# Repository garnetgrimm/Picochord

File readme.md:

# Picochord
An open source digital Omnichord clone based on the Raspberry Pi Pico. The firmware is currently configured to only generate audio from the input signals, but usb/analog midi support is in the works for the near future.

## Building the Firmware
The getting started guide has detailed instructions for building on each OS. https://datasheets.raspberrypi.com/pico/getting-started-with-pico.pdf

You will likely have to cd into the build directory to configure cmake and build.

## Circuits
The entire Picochord is comprised of three main subcircuits, all driven by the pico. 

* Keypad
* Strumpad
* Speaker amplifier

The PCB directory contains simulations, schematics, PCB's and screenshots for each of the circuits. The schematics/PCBs can be viewed with KiCad 6.0

## Chassis
The PCB's were screwed directly into a acrylic board. The only other required pieces were a battery holder and speaker holder which I have included STL's and FreeCad files for.

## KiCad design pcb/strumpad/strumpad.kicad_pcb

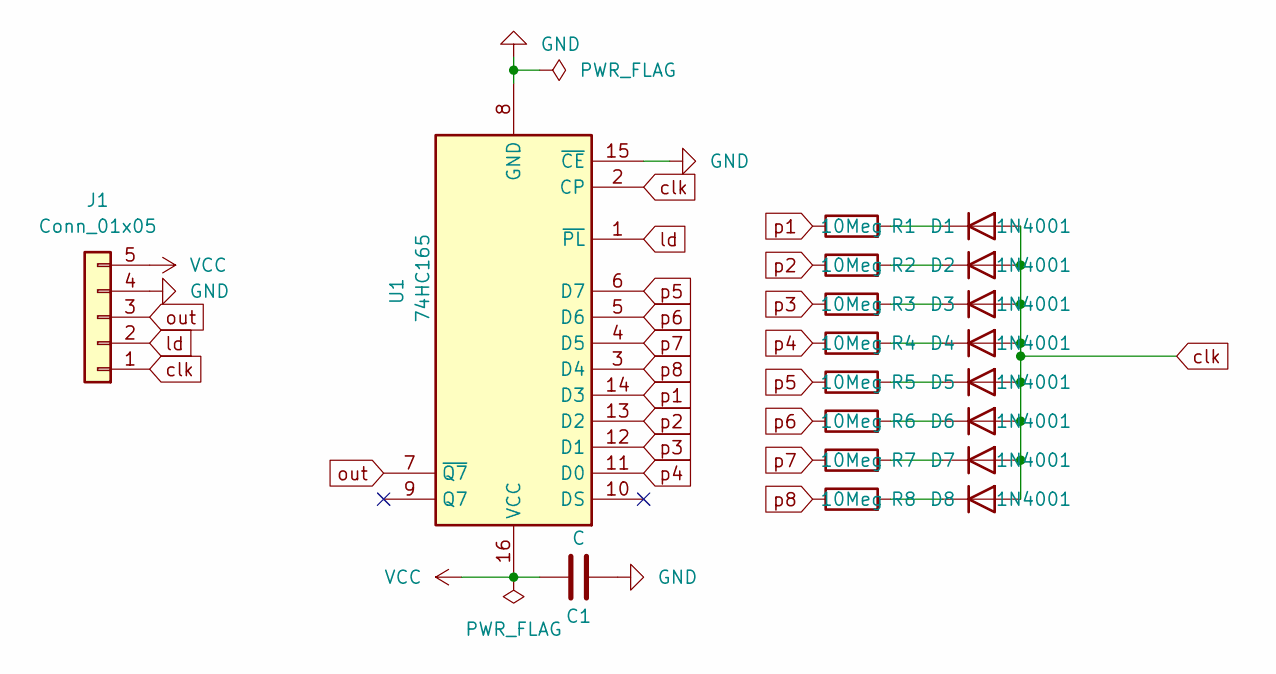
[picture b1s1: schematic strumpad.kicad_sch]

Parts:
C1: C; CP_Radial_D5.0mm_P2.50mm
D1, D2, D3, D4, D5, D6, D7, D8: 1N4001; D_DO-41_SOD81_P10.16mm_Horizontal
J1: Conn_01x05; PinSocket_1x05_P2.54mm_Vertical
R1, R2, R3, R4, R5, R6, R7, R8: 10Meg; R_Axial_DIN0204_L3.6mm_D1.6mm_P5.08mm_Horizontal
U1: 74HC165; DIP-16_W7.62mm_Socket

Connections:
GND: C1.2, J1.4, U1.8 (GND), U1.15 (~CE)
unnamed: D1.1 (K), R1.2
unnamed: D2.1 (K), R2.2
unnamed: D3.1 (K), R3.2
unnamed: D4.1 (K), R4.2
unnamed: D5.1 (K), R5.2
unnamed: D6.1 (K), R6.2
unnamed: D7.1 (K), R7.2
unnamed: D8.1 (K), R8.2
VCC: C1.1, J1.5, U1.16 (VCC)
clk: D1.2 (A), D2.2 (A), D3.2 (A), D4.2 (A), D5.2 (A), D6.2 (A), D7.2 (A), D8.2 (A), J1.1, U1.2 (CP)
ld: J1.2, U1.1 (~PL)
out: J1.3, U1.7 (~Q7)
p1: R1.1, U1.14 (D3)
p2: R2.1, U1.13 (D2)
p3: R3.1, U1.12 (D1)
p4: R4.1, U1.11 (D0)
p5: R5.1, U1.6 (D7)
p6: R6.1, U1.5 (D6)
p7: R7.1, U1.4 (D5)
p8: R8.1, U1.3 (D4)

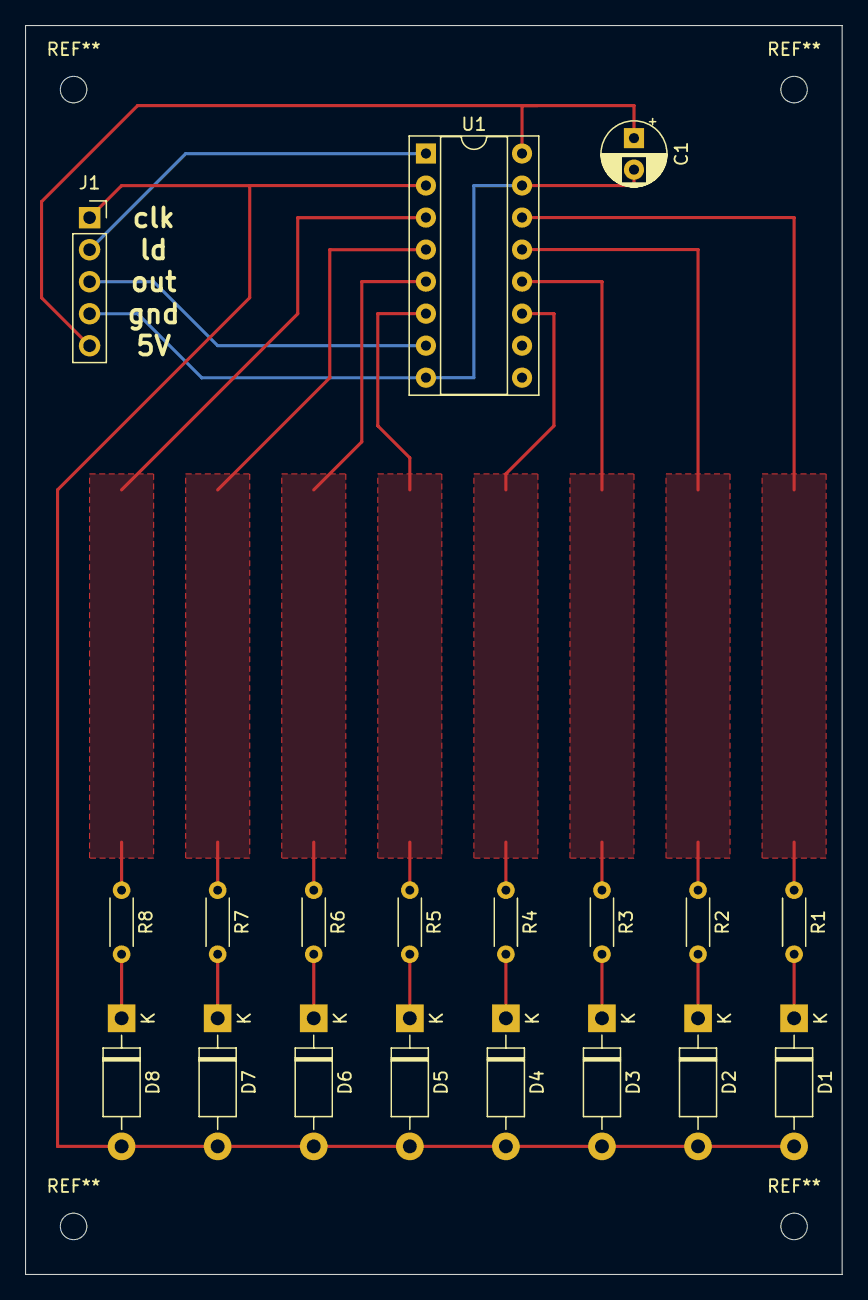
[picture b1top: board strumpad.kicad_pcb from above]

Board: 2 copper layers, 64.8 x 99.1 mm, 19 parts (0 on the bottom side), 21 nets.

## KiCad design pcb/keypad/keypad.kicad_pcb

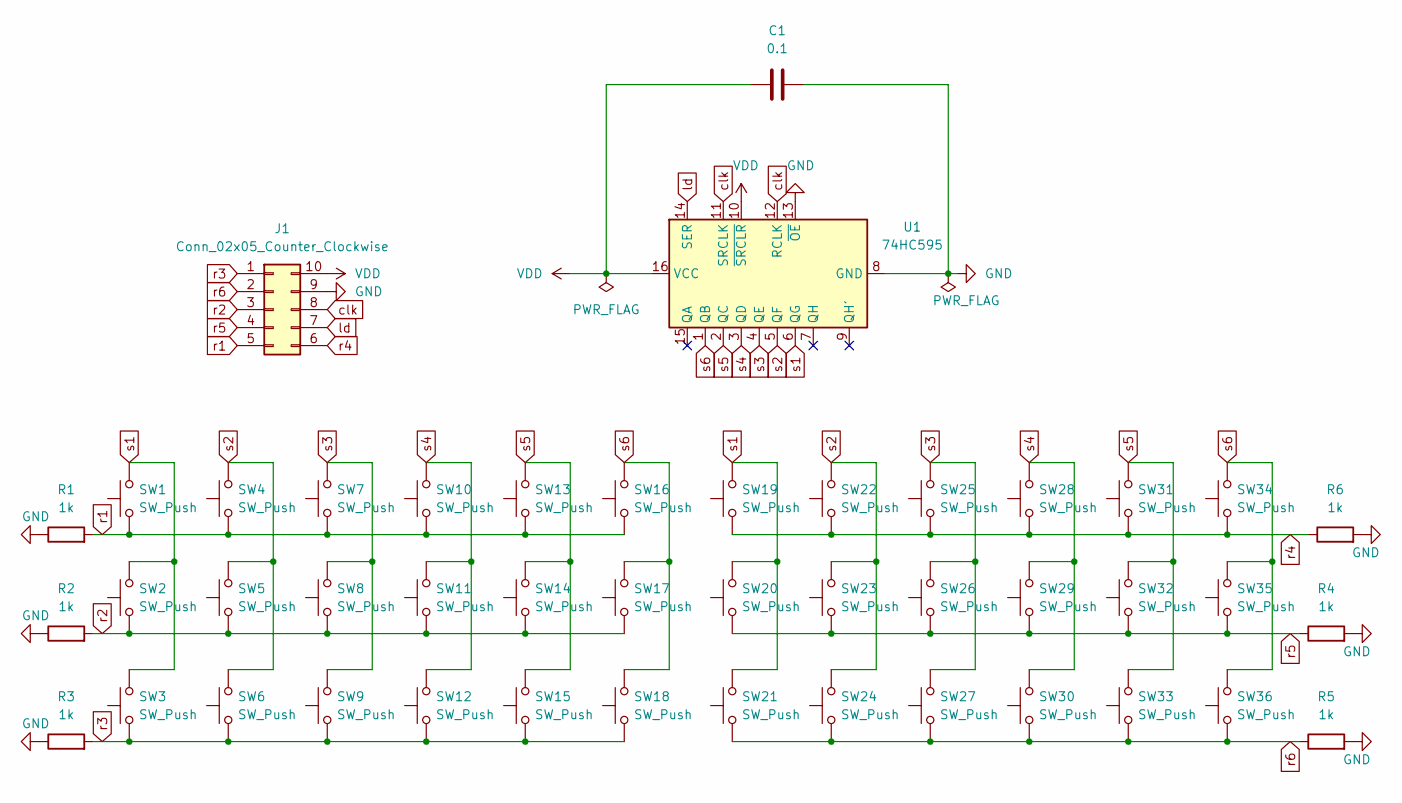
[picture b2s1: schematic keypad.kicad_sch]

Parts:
C1: 0.1; CP_Radial_D5.0mm_P2.50mm
J1: Conn_02x05_Counter_Clockwise; PinSocket_2x05_P2.54mm_Vertical
R1, R2, R3, R4, R5, R6: 1k; R_Axial_DIN0207_L6.3mm_D2.5mm_P2.54mm_Vertical
SW1, SW2, SW3, SW4, SW5, SW6, SW7, SW8, SW9, SW10, SW11, SW12, SW13, SW14, SW15, SW16, SW17, SW18, SW19, SW20, SW21, SW22, SW23, SW24, SW25, SW26, SW27, SW28, SW29, SW30, SW31, SW32, SW33, SW34, SW35, SW36: SW_Push; SW_PUSH_6mm
U1: 74HC595; DIP-16_W7.62mm_Socket

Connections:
GND: C1.2, J1.9, R1.1, R2.1, R3.1, R4.2, R5.2, R6.2, U1.8 (GND), U1.13 (~OE)
VDD: C1.1, J1.10, U1.10 (~SRCLR), U1.16 (VCC)
clk: J1.8, U1.11 (SRCLK), U1.12 (RCLK)
ld: J1.7, U1.14 (SER)
r1: J1.5, R1.2, SW1.1, SW4.1, SW7.1, SW10.1, SW13.1, SW16.1
r2: J1.3, R2.2, SW2.1, SW5.1, SW8.1, SW11.1, SW14.1, SW17.1
r3: J1.1, R3.2, SW3.1, SW6.1, SW9.1, SW12.1, SW15.1, SW18.1
r4: J1.6, R6.1, SW19.1, SW22.1, SW25.1, SW28.1, SW31.1, SW34.1
r5: J1.4, R4.1, SW20.1, SW23.1, SW26.1, SW29.1, SW32.1, SW35.1
r6: J1.2, R5.1, SW21.1, SW24.1, SW27.1, SW30.1, SW33.1, SW36.1
s1: SW1.2, SW2.2, SW3.2, SW19.2, SW20.2, SW21.2, U1.6 (QG)
s2: SW4.2, SW5.2, SW6.2, SW22.2, SW23.2, SW24.2, U1.5 (QF)
s3: SW7.2, SW8.2, SW9.2, SW25.2, SW26.2, SW27.2, U1.4 (QE)
s4: SW10.2, SW11.2, SW12.2, SW28.2, SW29.2, SW30.2, U1.3 (QD)
s5: SW13.2, SW14.2, SW15.2, SW31.2, SW32.2, SW33.2, U1.2 (QC)
s6: SW16.2, SW17.2, SW18.2, SW34.2, SW35.2, SW36.2, U1.1 (QB)

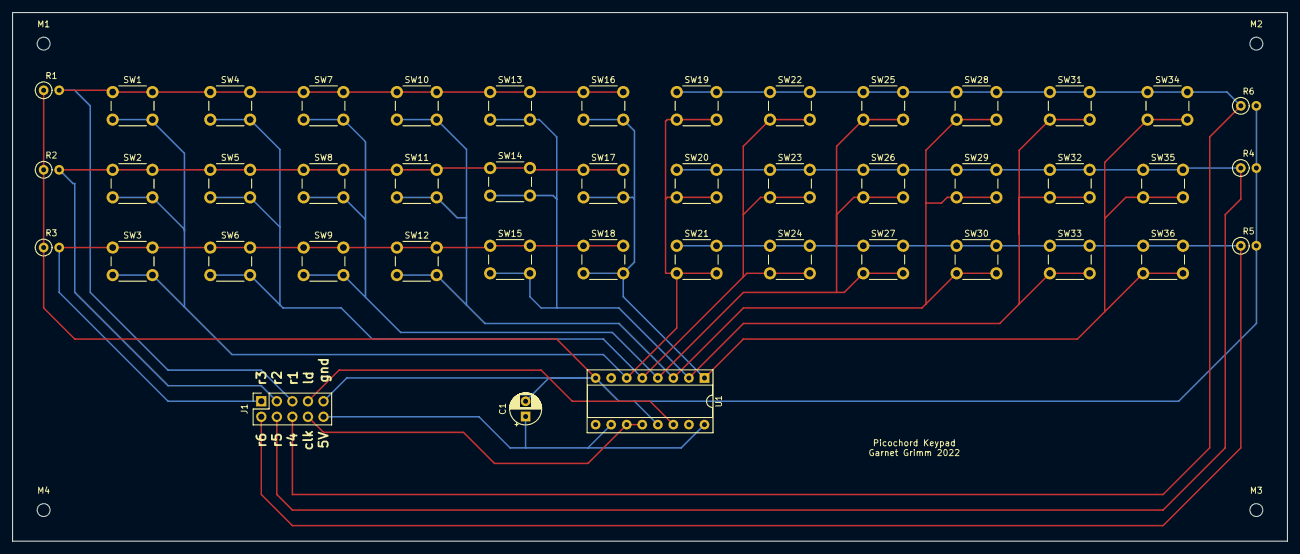
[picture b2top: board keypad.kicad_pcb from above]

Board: 2 copper layers, 208.3 x 86.4 mm, 49 parts (0 on the bottom side), 16 nets.

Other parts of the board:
M1, M2, M3, M4: MountingHole_2.1mm

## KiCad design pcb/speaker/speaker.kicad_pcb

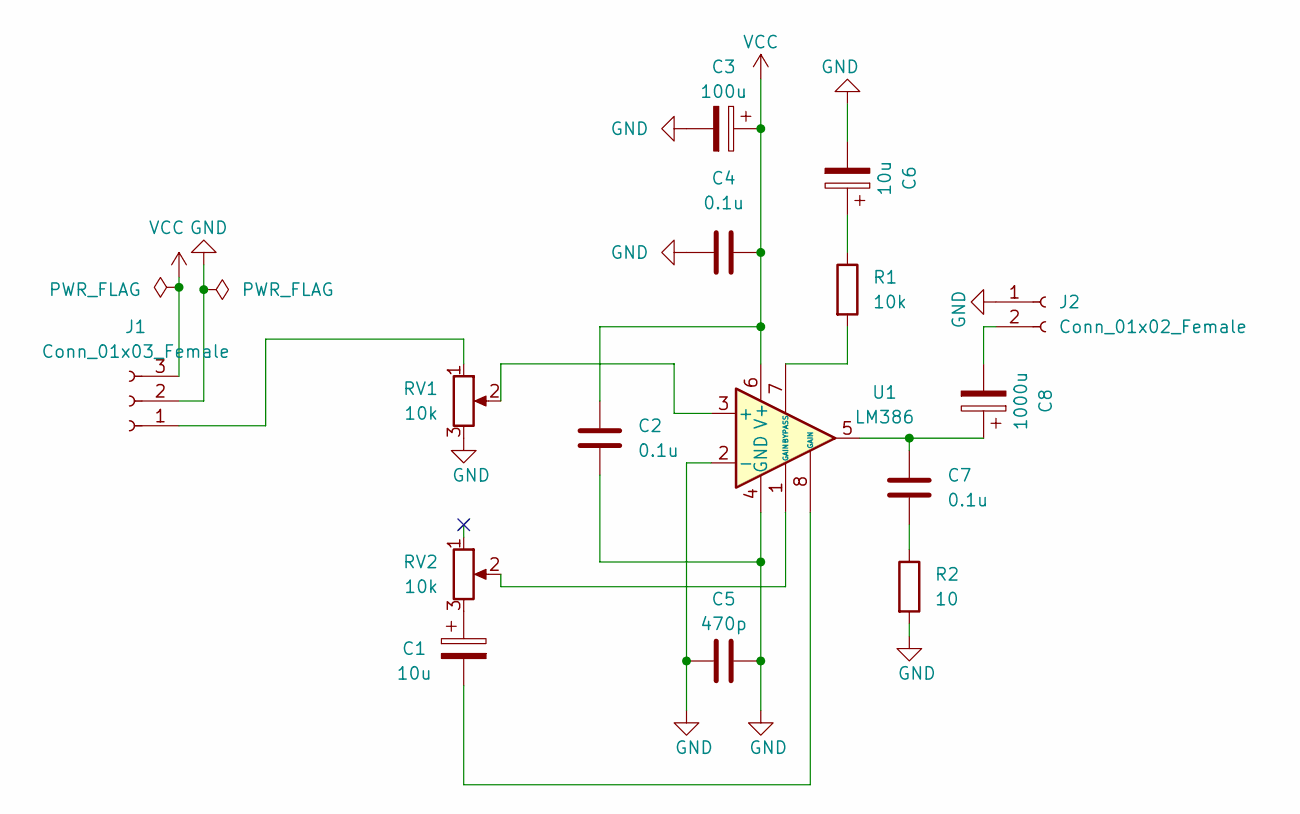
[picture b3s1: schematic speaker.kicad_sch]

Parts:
C1, C6: 10u; CP_Radial_D6.3mm_P2.50mm
C2, C4, C7: 0.1u; CP_Radial_D6.3mm_P2.50mm
C3: 100u; CP_Radial_D6.3mm_P2.50mm
C5: 470p; CP_Radial_D6.3mm_P2.50mm
C8: 1000u; CP_Radial_D6.3mm_P2.50mm
J1: Conn_01x03_Female; PinSocket_1x03_P2.54mm_Vertical
J2: Conn_01x02_Female; PinSocket_1x02_P2.54mm_Vertical
R1: 10k; R_Axial_DIN0207_L6.3mm_D2.5mm_P7.62mm_Horizontal
R2: 10; R_Axial_DIN0207_L6.3mm_D2.5mm_P7.62mm_Horizontal
RV1, RV2: 10k; Potentiometer_Alps_RK09Y11_Single_Horizontal
U1: LM386; DIP-8_W7.62mm_Socket

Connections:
GND: C2.1, C3.2, C4.1, C5.1, C5.2, C6.2, J1.2, J2.1, R2.2, RV1.3, U1.2 (-), U1.4 (GND)
unnamed: C1.1, RV2.3
unnamed: C1.2, U1.8 (GAIN)
unnamed: C6.1, R1.1
unnamed: C7.1, R2.1
unnamed: C7.2, C8.1, U1.5
unnamed: C8.2, J2.2
unnamed: R1.2, U1.7 (BYPASS)
unnamed: J1.1, RV1.1
unnamed: RV1.2, U1.3 (+)
unnamed: RV2.2, U1.1 (GAIN)
VCC: C2.2, C3.1, C4.2, J1.3, U1.6 (V+)

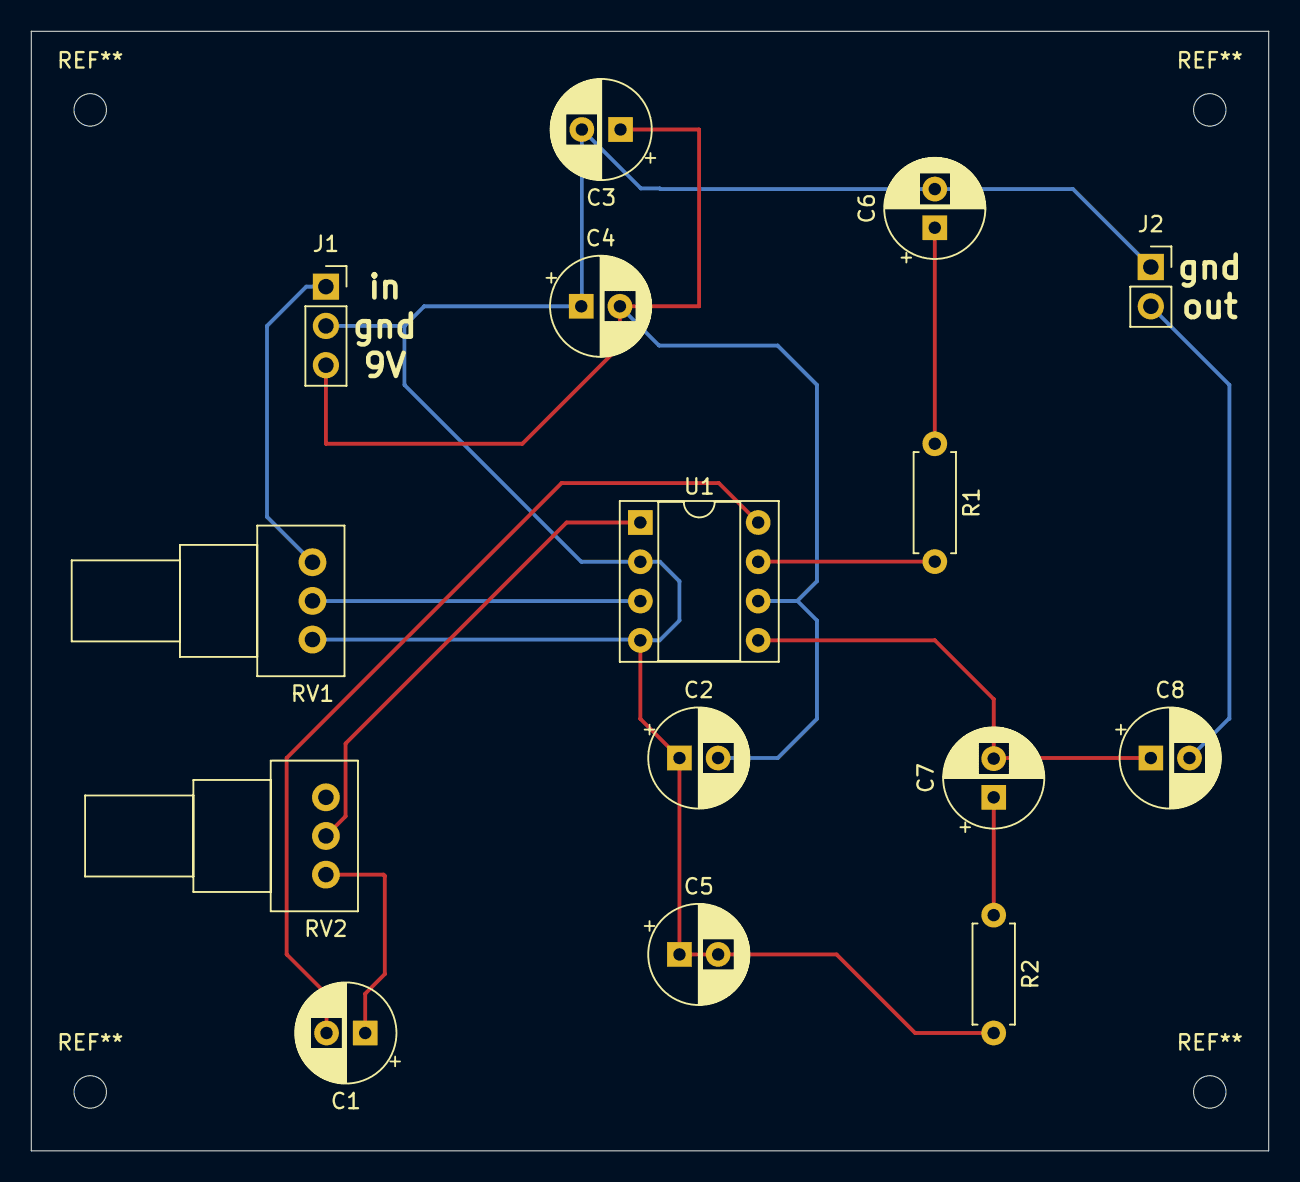
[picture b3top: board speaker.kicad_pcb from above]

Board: 2 copper layers, 80.0 x 72.4 mm, 15 parts (0 on the bottom side), 12 nets.

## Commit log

2022-04-25 init commit
2022-04-26 floats!
2022-04-26 strumpad
2022-04-26 got some button functionality
2022-04-26 renamed makefile
2022-04-28 cleaning up + phase offset
2022-04-29 WARNING: PROMISING BUT UNTESTED FULL CODE
2022-04-29 minor bug fixes and print statements!
2022-04-30 keypad routine switched from pwm based to timer based. Fixes a couple bugs and makes control logic easier
2022-04-30 remapped some pins
2022-04-30 keyboard now responds to last pressed
2022-05-03 decided to just emulate all the individual oscillators sorrynotsorry
2022-05-04 seperated oscillators from PWM and solved MAJOR ram issue
2022-05-06 added DC offset to signal
2022-05-07 WOWE working omnichord
2022-05-16 all together now
2022-05-19 support for 12 columns and start to fix strum problem
2022-05-19 some physical comonents
2022-05-20 modeled PCB
2022-05-20 speaker
2022-05-20 annotated pinout
2022-05-20 screenshots
2022-05-20 readme
2022-05-23 strumpad update'
2022-06-19 swapping out custom hardware driver code for cap1188
2022-06-24 spi implementation
2022-06-25 pin remap
